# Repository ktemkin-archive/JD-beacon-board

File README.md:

Junior Design Competition Beacons
===============

This repository contains a collection of hardware and software used for the Binghamton University Junior Design Competition-- the centerpiece for a junior-level design course in the EECE department of Binghamton University. The repository can be considered a work in progess, though many components of the game are complete and tested.

##Game

The basics of the game-- and the gameplay rules-- will be described here once the challenge has been formally announced.

##Contents:

* _board software_: The low-level embedded software that drives the Beacon gameplay elements. This software should be programmed to the ATMega32U4 on the beacon PCB.
* _enclosure hardware_: A set of technical drawings which show how to create a Beacon, the core element of the gameplay field.  The vector images for these technical drawins can be lasercut to create an actual beacon enclosure ("beacon tower").
* _pc software_: A collection of PC software designed to drive the competition. This collection contains a set of utilities with which to test a student robot; and will contain the final software used to run the robotics competition.
* _pcb hardware_: The schematics, bill of materials, and PCB layout for the core PCB that drives each beacon element. These can be used to create a the core beacon element.

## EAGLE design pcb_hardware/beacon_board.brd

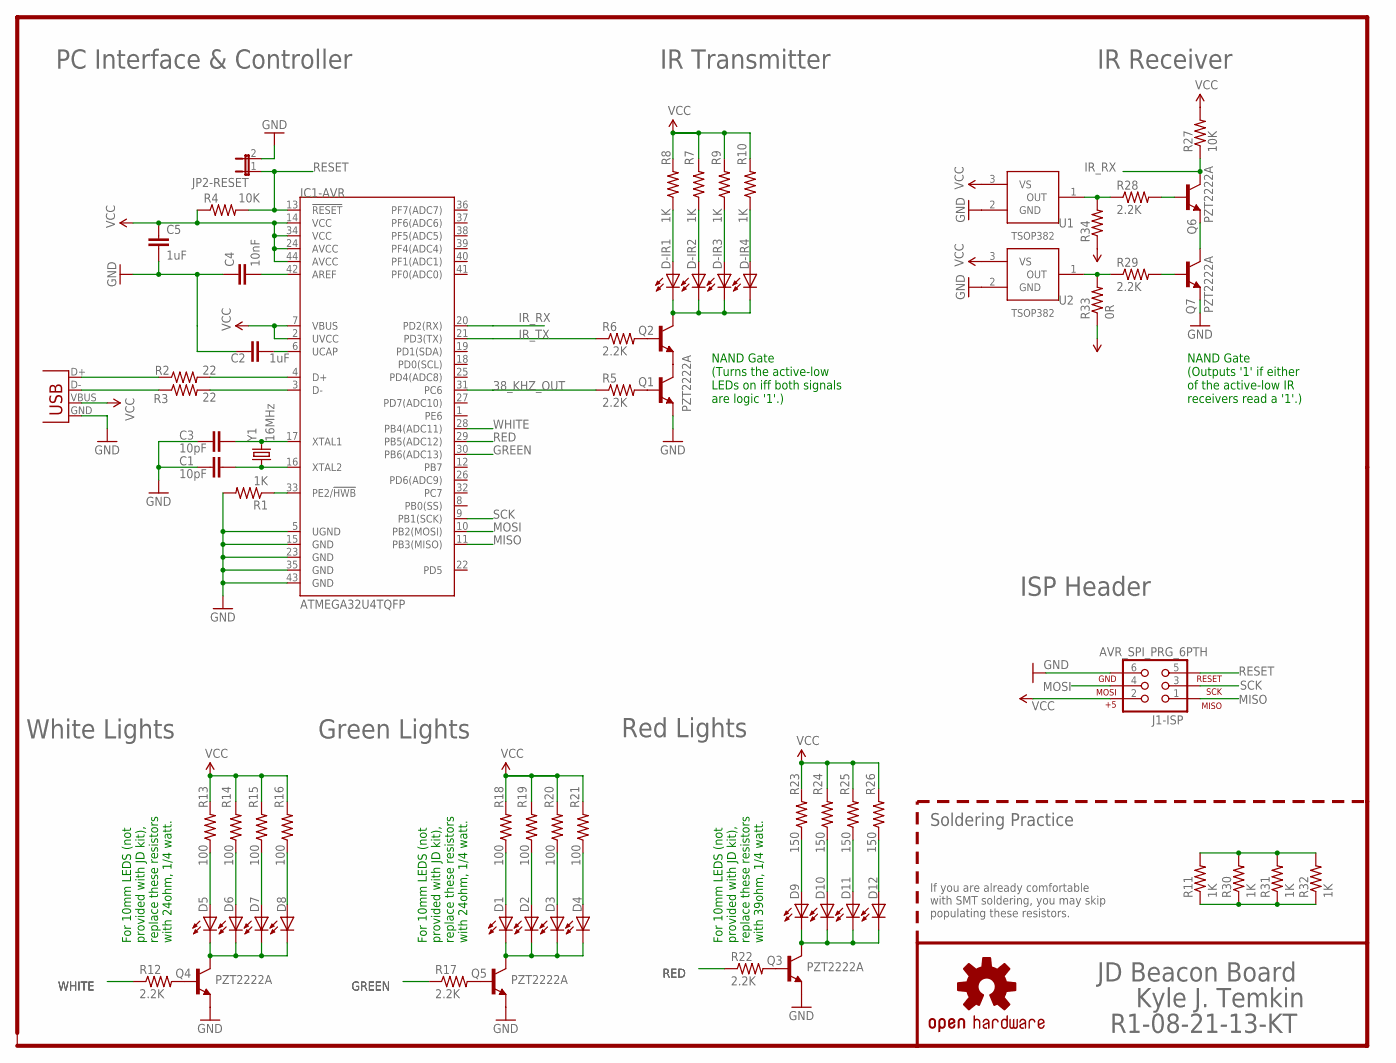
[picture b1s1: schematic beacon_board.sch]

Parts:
C1, C3: 10pF; 0805
C2, C5: 1uF; 0805
C4: 10nF; 0805
D1, D2, D3, D4, D5, D6, D7, D8, D9, D10, D11, D12: LED10MM
D-IR1, D-IR2, D-IR3, D-IR4: LED5MM
IC1-AVR: ATMEGA32U4TQFP; SPARKFUN-DIGITALIC_TQFP44
J1-ISP: AVR_SPI_PRG_6PTH; 2X3
JP1: USBSMD; USB-MINIB
JP2-RESET: JUMPER-2SMD-NO; SJ_2S-NO
LOGO1: OSHW-LOGOM; OSHW-LOGO-M
Q1, Q2, Q3, Q4, Q5, Q6, Q7: PZT2222A; SOT223
R1, R7, R8, R9, R10, R11, R30, R31, R32: 1K; 0805
R2, R3: 22; 0805
R4, R27: 10K; 0805
R5, R6, R12, R17, R22, R28, R29: 2.2K; 0805
R13, R14, R15, R16, R18, R19, R20, R21: 100; 0805
R23, R24, R25, R26: 150; 0805
R33: 0R; 0805
R34: RESISTOR0805-RES; 0805
U1, U2: TSOP382
U$1: BINGHAMTON-EECE-TEXT
Y1: 16MHz; HC49US

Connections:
38_KHZ_OUT: IC1-AVR.31 (PC6), R5.1
D1: D1.C, D2.C, D3.C, D4.C, Q5.2 (C), Q5.4 (C)
D2: D9.C, D10.C, D11.C, D12.C, Q3.2 (C), Q3.4 (C)
D9: D5.C, D6.C, D7.C, D8.C, Q4.2 (C), Q4.4 (C)
GND: C1.1, C2.1, C3.1, C4.1, C5.2, IC1-AVR.5 (UGND), IC1-AVR.15 (GND), IC1-AVR.23 (GND), IC1-AVR.35 (GND), IC1-AVR.43 (GND), J1-ISP.6, JP1.GND, JP2-RESET.2, Q1.3 (E), Q3.3 (E), Q4.3 (E), Q5.3 (E), Q7.3 (E), R1.2, U1.2 (GND), U2.2 (GND)
GREEN: IC1-AVR.30 (PB6(ADC13)), R17.1
IR_RX: IC1-AVR.20 (PD2(RX)), Q6.2 (C), Q6.4 (C), R27.1
IR_TX: IC1-AVR.21 (PD3(TX)), R6.1
MISO: IC1-AVR.11 (PB3(MISO)), J1-ISP.1
MOSI: IC1-AVR.10 (PB2(MOSI)), J1-ISP.4
unnamed: IC1-AVR.4 (D+), R2.2
unnamed: IC1-AVR.3 (D-), R3.2
unnamed: JP1.D+, R2.1
unnamed: JP1.D-, R3.1
unnamed: C2.2, IC1-AVR.6 (UCAP)
unnamed: C3.2, IC1-AVR.17 (XTAL1), Y1.2
unnamed: C1.2, IC1-AVR.16 (XTAL2), Y1.1
unnamed: IC1-AVR.33 (PE2/!HWB), R1.1
unnamed: Q4.1 (B), R12.2
unnamed: Q5.1 (B), R17.2
unnamed: C4.2, IC1-AVR.42 (AREF)
unnamed: Q2.1 (B), R6.2
unnamed: Q1.1 (B), R5.2
unnamed: Q1.2 (C), Q1.4 (C), Q2.3 (E)
unnamed: D-IR1.K (C), D-IR2.K (C), D-IR3.K (C), D-IR4.K (C), Q2.2 (C), Q2.4 (C)
unnamed: D-IR1.A, R8.1
unnamed: D1.A, R18.1
unnamed: D5.A, R13.1
unnamed: D-IR3.A, R9.1
unnamed: D7.A, R15.1
unnamed: D3.A, R20.1
unnamed: Q3.1 (B), R22.2
unnamed: D9.A, R23.1
unnamed: D11.A, R25.1
unnamed: Q6.3 (E), Q7.2 (C), Q7.4 (C)
unnamed: R28.1, R34.2, U1.1 (OUT)
unnamed: Q6.1 (B), R28.2
unnamed: Q7.1 (B), R29.2
unnamed: R29.1, R33.2, U2.1 (OUT)
unnamed: R11.2, R30.2, R31.2, R32.2
unnamed: R11.1, R30.1, R31.1, R32.1
RED: IC1-AVR.29 (PB5(ADC12)), R22.1
RESET: IC1-AVR.13 (!RESET), J1-ISP.5, JP2-RESET.1, R4.2
SCK: IC1-AVR.9 (PB1(SCK)), J1-ISP.3
VCC: C5.1, IC1-AVR.2 (UVCC), IC1-AVR.7 (VBUS), IC1-AVR.14 (VCC), IC1-AVR.24 (AVCC), IC1-AVR.34 (VCC), IC1-AVR.44 (AVCC), J1-ISP.2, JP1.VBUS, R4.1, R7.2, R8.2, R9.2, R10.2, R13.2, R14.2, R15.2, R16.2, R18.2, R19.2, R20.2, R21.2, R23.2, R24.2, R25.2, R26.2, R27.2, R33.1, R34.1, U1.3 (VS), U2.3 (VS)
VCC1: D-IR2.A, R7.1
VCC2: D6.A, R14.1
VCC3: D-IR4.A, R10.1
VCC4: D8.A, R16.1
VCC5: D2.A, R19.1
VCC6: D4.A, R21.1
VCC7: D10.A, R24.1
VCC8: D12.A, R26.1
WHITE: IC1-AVR.28 (PB4(ADC11)), R12.1

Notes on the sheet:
IR Transmitter
PC Interface & Controller
For 10mm LEDS (not provided with JD kit), replace these resistors with 24ohm, 1/4 watt.
For 10mm LEDS (not provided with JD kit), replace these resistors with 39ohm, 1/4 watt.
NAND Gate (Turns the active-low LEDs on iff both signals are logic '1'.)
NAND Gate (Outputs '1' if either of the active-low IR receivers read a '1'.)
IR Receiver
ISP Header
Red Lights
Green Lights
White Lights
JD Beacon Board
Kyle J. Temkin
R1-08-21-13-KT
Soldering Practice
If you are already comfortable with SMT soldering, you may skip populating these resistors.

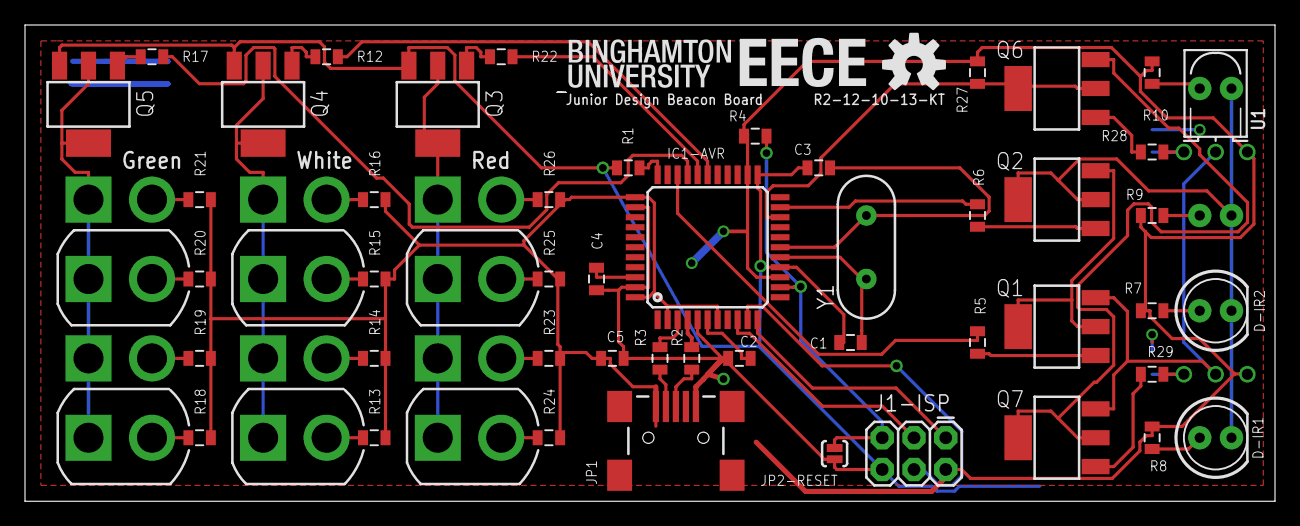
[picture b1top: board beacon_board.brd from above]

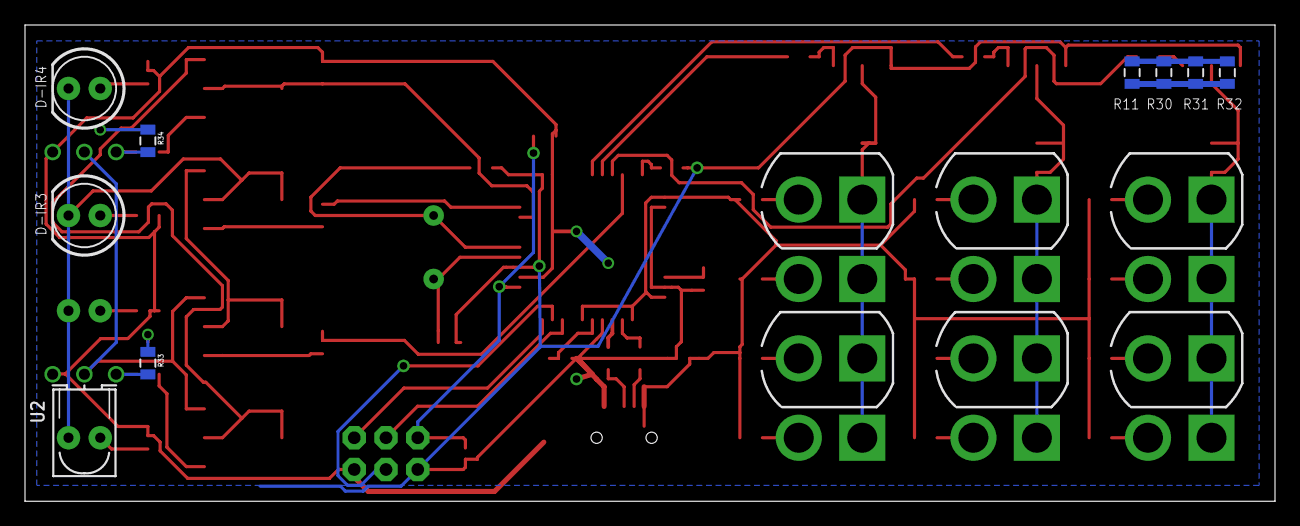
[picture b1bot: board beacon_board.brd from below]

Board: 2 copper layers, 100.0 x 38.1 mm, 71 parts (15 on the bottom side), 54 nets.

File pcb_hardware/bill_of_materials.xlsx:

Part Designator | Qty | Value | Device | Package | Manufacturer P/N | Supplier | Supplier P/N | Price at Mfg Qty |  | Description | Extended Price | Qty to Purchase | Qty In Stock (1/2) | Total Cost (at Mfg Qty)
D1-4 | 0.16 | - | LED5MM | LED5MM | YSL-R542G5C-A14 | Sparkfun | COM-09661 | 7.16 |  | Beacon LEDs(Green), 5mm or 10mm | 1.1456 | 24 | 89 | 171.84
D5-8 | 0.16 | - | LED5MM | LED5MM | YSL-R547W2C-A13 | Sparkfun | COM-09850 | 7.16 |  | Beacon LEDS (White), 5mm or 10mm | 1.1456 | 24 | 154 | 171.84
D9-12 | 0.16 | - | LED5MM | LED5MM | YSL-R531R3C-A13 | Sparkfun | COM-09660 | 7.16 |  | Beacon LEDs (Red), 5mm or 10mm | 1.1456 | 24 | 106 | 171.84
DIR1-4 | 4 | - | LED5MM | LED5MM | IR7393C | Digikey | 1080-1087-ND | 0.112 |  | IR LED | 0.448 | 600 |  | 67.2
U1-2 | 2 | - | TSOP382 | TSOP382 | TSOP38238 | Digikey | 751-1227-ND | 0.559 |  | IR Receiver | 1.118 | 300 |  | 167.7
R13-16, R18-R21 | 8 | 100 | RESISTOR0805-RES | 0805 | ERJ-6GEYJ101V | Digikey | P100ACT-ND | 0.00544 |  | Resistor | 0.04352 | 1200 |  | 6.528
R4, R27 | 2 | 10K | RESISTOR0805-RES | 0805 | ERJ-6GEYJ103V | Digikey | P10KACT-ND | 0.01104 |  | Resistor | 0.02208 | 300 |  | 3.312
C4 | 1 | 10nF | CAP0805 | 0805 | CL21B103KBANNNC | Digikey | 1276-1015-2-ND | 0.0142 |  | Capacitor | 0.0142 | 150 |  | 2.13
C1, C3 | 2 | 10pF | CAP0805 | 0805 | CL21C100JBANNNC | Digikey | 1276-1109-1-ND | 0.018 |  | Capacitor | 0.036 | 300 |  | 5.4
R23-26 | 4 | 150 | RESISTOR0805-RES | 0805 | ERJ-6GEYJ151V | Digikey | P150ACT-ND | 0.00816 |  | Resistor | 0.03264 | 600 |  | 4.896
Y1 | 1 | 16MHz | CRYSTALHC49US | HC49US | ATS16B | Digikey | CTX1085-ND | 0.24 |  | Crystal Osc. | 0.24 | 150 |  | 36
R1, R7-11, R30-R32 | 9 | 1K | RESISTOR0805-RES | 0805 | RC0805FR-071KL | Digikey | 311-1.00KCRCT-ND | 0.00381 |  | Resistor | 0.03429 | 1350 |  | 5.1435
C2, C5 | 2 | 1uF | CAP0805 | 0805 | CC0805ZRY5V8BB105 | Digikey | 311-1358-1-ND | 0.02204 |  | Capacitor | 0.04408 | 300 |  | 6.612
R5-6, R12, R17, R22, R28-29 | 7 | 2K2 (2.2k) | RESISTOR0805-RES | 0805 | ERJ-6GEYJ222V | Digikey | P2.2KACT-ND | 0.00544 |  | Resistor | 0.03808 | 1050 |  | 5.712
R2-3 | 2 | 22 | RESISTOR0805-RES | 0805 | RPC0805JT22R0 | Digikey | RPC0805JT22R0CT-ND | 0.06824 |  | Resistor | 0.13648 | 300 |  | 20.472
IC1 | 1 |  | ATMEGA32U4TQFP | TQFP44 | ATMEGA32U4-AUR | Digikey | ATMEGA32U4-AURCT-ND | 4.3305 |  | USB-AVR Microcontroller | 4.3305 | 150 |  | 649.575
Q1-7 | 7 |  | PZT2222A | SOT223 | PZT2222AT1G | Digikey | PZT2222AT1GOSTR-ND | 0.1032 |  | NPN Transistor | 0.7224 | 1050 |  | 108.36
JP1 | 1 |  | USBSMD | USB-MINIB | 1734035-2 | Newark | 16M3869 | 0.8 |  | Mini-USB-B Connector | 0.8 | 150 |  | 120
- | 1 |  | PCB | - | JDBB-R2 | Advanced Circuits |  | 5.763 |  | Printed Circuit Board | 5.763 | 200 |  | 864.45
 |  |  |  |  |  |  |  |  |  |  |  |  |  |  |  | 1089.0405
 |  |  |  |  |  | Mfg Qty | 150 |  |  | Total | 14.96887 |  |  | 2589.0105
 |  |  |  |  |  |  |  |  |  | Budget | 21.1666666666667 |  |  | 3175
 |  |  |  |  |  |  |  |  |  | Digi-Key | 1098
 |  |  |  |  |  |  |  |  |  | Sparkfun | 515.52
 |  |  |  |  |  |  |  |  |  | Newark | 120
 |  |  |  |  |  |  |  |  |  | Advanced Circuits | 864.45
 |  |  |  |  |  |  |  |  |  |  | 2597.97 | 0.818258267716536

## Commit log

2013-07-23 Add USB-to-serial library.
2013-07-27 implement light control and IR carrier wave
2013-08-15 implement basic PC comm and beacon state
2013-08-16 implement PC comm and basic PC backend
2013-08-16 improve PC communciation
2013-08-17 Fixes state reversion glitch.
    -Fixes a glitch in which certain control packets incorrectly caused a state reversion,
    as a left-over piece of the data buffer was incorrectly interpreted as the current state.
    -Normalizes all "invalid beacon IDs" to the number 31, rather than the (equivalent) -1.
2013-08-17 Implement IR transmission and misc improvements.
    -Implement outgoing, asynchronous IR transmission.
    -Improve naming conventions for typedef'd structs.
    -Clean up main.h
    -Implement basic random seed logic.
2013-08-17 Implement backend IR reception.
2013-08-17 Implements (untested) board-side game logic
2013-08-18 Modify PJRC's usb-serial lib to suppress a warning.
2013-08-19 Finish basic functionality of beacon board firmware
2013-08-19 Create initial incomplete work on PCB.
2013-08-20 Finish initial unchecked schematic capture
2013-08-20 Add scratch work for board layout
2013-08-20 Complete alpha prototype for PCB
2013-08-20 Add renders of the prototype PCB
2013-08-21 Update bill of materials with part numbers
2013-08-21 Finish R1 of the beacon board PCB.
2013-10-06 Abstracts PWM timer functionality to a library.
    TIMER1 is currently used to drive LED dimming via PWM. Prior to this commit,
    it was coupled to the light module, and thus could not be used for other
    purposes.
    This commit decouples that module, allowing the timer to be used
    to generate an additional 1Hz signal (which will be useful in future
    IR communications procedures).
2013-10-06 Adds AVR-DFU options to the board software's makefile.
    These options allow the board to rapidly be programmed using the
    Device Firmware Upgrade mode.
2013-10-07 Add missing dependency to the beacon library.
    Adds the 'forwarable' module back to the beacon board library,
    which fixers a dependency issue when the libraries were called
    in a non-standard order.
2013-10-07 Change to sparse serial transmission.
    -Adjusts serial transmission to occur one time per second,
    rather than as fast as possible. This encourages the contestants
    to use the bright lights atop the beacon to locate each beacon,
    rather than a constant stream of IR.
    -Beacons now transmit a new pseudo-random code every second,
    rather than the same code repeatedly.
2013-10-16 Finish initial beacon board and improve IR library
2013-11-18 inital work on webapp
2013-11-18 relocate code to JDBeacon namespace
2013-11-18 further work on webapp
2013-12-04 add beacon enclosure
2013-12-13 Add parallell resistors for TSOP IR receivers
2013-12-28 first working version of webapp
2014-01-03 add new beacon images
2014-01-03 update beacon board for final DFM steps
2014-01-03 fix formatting on README
2014-01-24 Add basic start of gameplay documentation.
2014-01-27 [GAMEPLAY] Add basic contest rules.
2014-01-27 [BOARD_SOFT] Add backend debug SPI interface.
2014-01-27 [PCB] Add SMD distribution sheet ("coupon").
2014-02-03 [PCB] Add initial assembly plan.
2014-02-06 [PC_SOFT] Initial working version of PC test software.
    Still requires Windows / OS X integration.
2014-02-09 [PC_SOFTWARE] Add tentative WMI interface for Windows.
2014-02-15 [PCB] Updated documentation.
2014-04-13 [BOARD_SOFT] Changes the unused inputs so they're "pulled up" to VDD.
    This change reduces the device's power consumption.
2014-04-14 [PC_SOFT] Add diagnostic information regarding IR claiming to the beacon tester.
2014-04-14 [BOARD_SOFT] Update the board software to provide diganostic information.
2014-04-14 [ENCLOSURE] Add mechanical drawings for the enclosure.
2014-04-14 [DOCS] Add assets to rules.
2014-04-14 [PCB] Update PCB assets.
2014-05-01 Add udev enumerator, which optimizes identificatin on Linux.
2014-05-01 Update gitignore to hide packagine details for Bundler.
2014-05-01 Add support for guard-based restarting of Sinatra.
2014-05-01 Add basic competitions support to the package.
2014-05-03 Fix missing rubdev dependency.
2014-05-04 Add more developed competition software.
2014-05-09 Add beacon freeze at the end of the competition.
    This makes for a more dramatic ending!
2014-05-12 Update responder.
2014-05-15 [BOARD_SOFT] Minor pre-competition updates.
2014-05-15 Late competition additions.
2014-05-15 Set default round length to 180 seconds.
2015-04-21 Ensure devices are sorted by serial
2015-04-21 Improve serial-sorting code in udev_enumerator
2015-04-21 Remove Gemfile.lock to fix issue building dependencies
    nio4r and serialport did not build correctly when their version were
    frozen.

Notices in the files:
parts and their libraries:
SparkFun-Aesthetics: Licensing: CC v3.0 Share-Alike You are welcome to use this library for commercial purposes.
